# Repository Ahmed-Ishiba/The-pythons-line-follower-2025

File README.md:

# Robocup-The Pythons

This is a documentation of our journey in the Robocup competition in line-follower category, the team members are Ahmed Ibrahim Elsayed (me), Moaz Ahmed, Eyad Ahmed, Nour Eldin Raoof each are responsible for the programming , electrical and Mechanical part of the robot respectively and our coach Omar Ahmed Khaled.

This documentation will list the components used , the thought process that went into making this robot and the algorithm of our line-following and evacuation zone

## Compontents used:
| Name | Price | Weight | Link|
|------|-------|--------|-----|
|Pololu wheels|9.95 USD|23gm|https://www.pololu.com/product/3691|
|Omni wheels|35 USD| 49gm|https://www.robotshop.com/products/70mm-omni-wheel-4mm-bore |
|133rpm Motors| 360 EGP|88gm|https://makerselectronics.com/product/dc-motor-with-gear-box-jga25-370-12v-133rpm-20kg-cm |
|Raspberry pi5 8gb ram| 80USD|76gm|https://www.adafruit.com/product/5813|
|Raspberry pi camera module3|35 USD|5gm|https://www.adafruit.com/product/5658|
|Adafruit DRV8871 motor driver|7.5 USD|5gm|https://www.adafruit.com/product/3190|
|Adafruit Time of Flight sensor|14.95 USD|2gm|https://www.adafruit.com/product/3317|
|10 DOF IMU|920 EGP|2gm|https://store.fut-electronics.com/products/10-dof-imu-mpu9250-bmp280?_pos=3&_sid=8a9a77714&_ss=r |
|InfraRed obstacle sensor|75 EGP|3gm|https://store.fut-electronics.com/products/infrared-obstacle-avoidance-sensor-ky-032?_pos=1&_sid=9cff58162&_ss=r|
|Microservo MG90S|140 EGP|17gm|https://makerselectronics.com/product/micro-servo-mg90s-full-metal-gear-180-degree|
|Hiwonder full metal gear|18.99 USD |101gm|https://www.hiwonder.com/products/hps-2018?_pos=16&_sid=3165c6d7c&_ss=r|
|XL 4015 step down dc convertor|115 EGP| 21 gm|https://makerselectronics.com/product/xl4015-step-down-dc-module-with-cv-cc-control|
|LM-2596S DC-DC convertor| 55 EGP |13gm|https://makerselectronics.com/product/lm2596s-dc-dc-converter-3a-step-down-module|
|XL-4016 Step down convertos| 260 EGP|75 gm | https://ampere-electronics.com/product/xl4016-dc-dc-step-down-converter-module-12a-300w/|
|Cytron dual channel motor driver| 1750 EGP | 33gm| https://store.fut-electronics.com/products/dual-channel-dc-motor-driver-10a-each|

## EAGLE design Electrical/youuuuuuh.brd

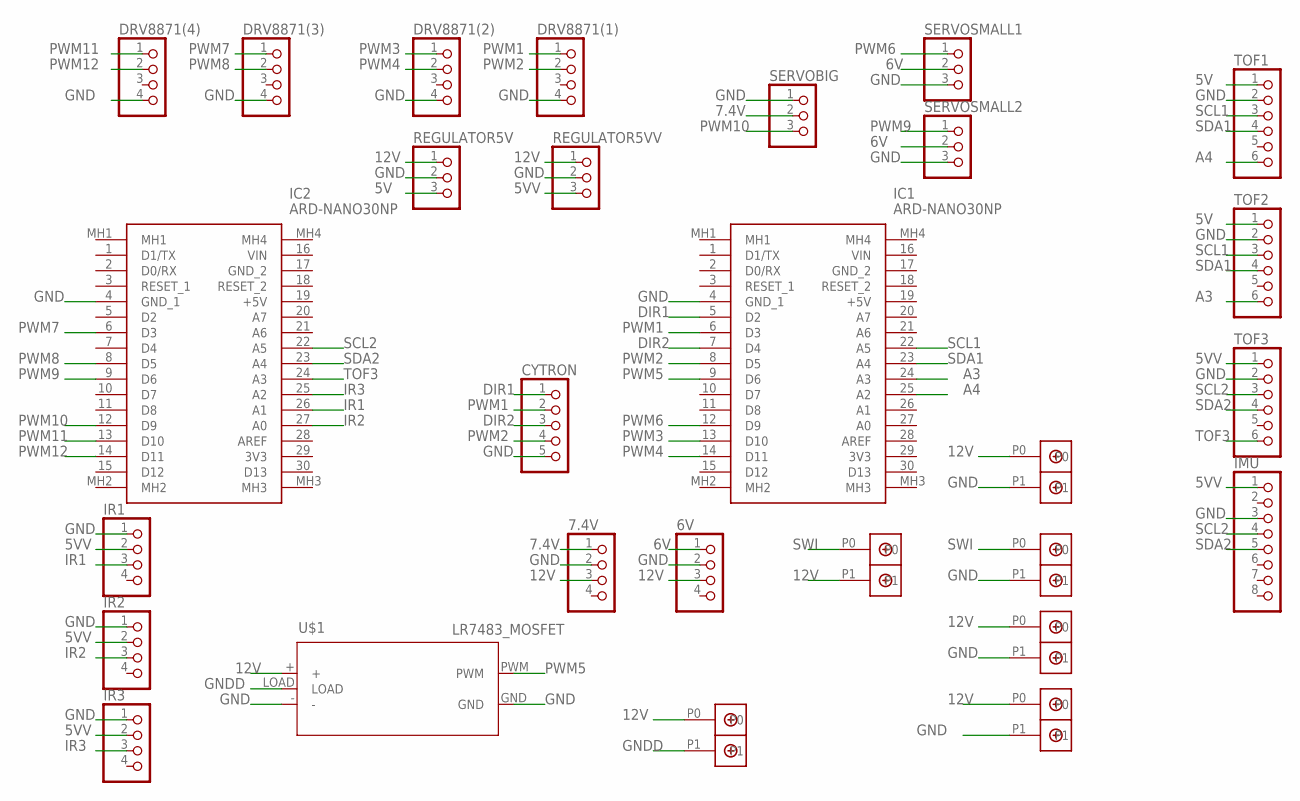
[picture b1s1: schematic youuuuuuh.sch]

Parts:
6V, 7.4V: PINHD-1X4; 1X04
BATERY: DBCONN-1X2
BUCKSERVO: DBCONN-1X2
CYTRON: PINHD-1X5; 1X05
CYTRONPOWER: DBCONN-1X2
DRV8871(1), DRV8871(2), DRV8871(3), DRV8871(4): PINHD-1X4; 1X04
IC1, IC2: ARD-NANO30NP; ARDNANO30NP
IMU: PINHD-1X8; 1X08
IR1, IR2, IR3: PINHD-1X4; 1X04
LEDS1, LEDS2, LEDS3: DBCONN-1X2
REGULATOR5V, REGULATOR5VV: PINHD-1X3; 1X03
SERVOBIG: PINHD-1X3; 1X03
SERVOSMALL1, SERVOSMALL2: PINHD-1X3; 1X03
TOF1, TOF2, TOF3: PINHD-1X6; 1X06
U$1: LR7483_MOSFET

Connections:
5V: REGULATOR5V.3, TOF1.1, TOF2.1
5VV: IMU.1, IR1.2, IR2.2, IR3.2, REGULATOR5VV.3, TOF3.1
6V: 6V.1, SERVOSMALL1.2, SERVOSMALL2.2
7.4V: 7.4V.1, SERVOBIG.2
12V: 6V.3, 7.4V.3, BUCKSERVO.P0, CYTRONPOWER.P0, LEDS1.P1, LEDS2.P0, LEDS3.P0, REGULATOR5V.1, REGULATOR5VV.1, U$1.+
A3: IC1.24 (A3), TOF2.6
A4: IC1.25 (A2), TOF1.6
DIR1: CYTRON.1, IC1.5 (D2)
DIR2: CYTRON.3, IC1.7 (D4)
GND: 6V.2, 7.4V.2, BATERY.P1, BUCKSERVO.P1, CYTRON.5, CYTRONPOWER.P1, DRV8871(1).4, DRV8871(2).4, DRV8871(3).4, DRV8871(4).4, IC1.4 (GND_1), IC2.4 (GND_1), IMU.3, IR1.1, IR2.1, IR3.1, LEDS2.P1, REGULATOR5V.2, REGULATOR5VV.2, SERVOBIG.1, SERVOSMALL1.3, SERVOSMALL2.3, TOF1.2, TOF2.2, TOF3.2, U$1.-, U$1.GND
GNDD: LEDS3.P1, U$1.LOAD
IR1: IC2.26 (A1), IR1.3
IR2: IC2.27 (A0), IR2.3
IR3: IC2.25 (A2), IR3.3
PWM1: CYTRON.2, DRV8871(1).1, IC1.6 (D3)
PWM2: CYTRON.4, DRV8871(1).2, IC1.8 (D5)
PWM3: DRV8871(2).1, IC1.13 (D10)
PWM4: DRV8871(2).2, IC1.14 (D11)
PWM5: IC1.9 (D6), U$1.PWM
PWM6: IC1.12 (D9), SERVOSMALL1.1
PWM7: DRV8871(3).1, IC2.6 (D3)
PWM8: DRV8871(3).2, IC2.8 (D5)
PWM9: IC2.9 (D6), SERVOSMALL2.1
PWM10: IC2.12 (D9), SERVOBIG.3
PWM11: DRV8871(4).1, IC2.13 (D10)
PWM12: DRV8871(4).2, IC2.14 (D11)
SCL1: IC1.22 (A5), TOF1.3, TOF2.3
SCL2: IC2.22 (A5), IMU.4, TOF3.3
SDA1: IC1.23 (A4), TOF1.4, TOF2.4
SDA2: IC2.23 (A4), IMU.5, TOF3.4
SWI: BATERY.P0, LEDS1.P0
TOF3: IC2.24 (A3), TOF3.6

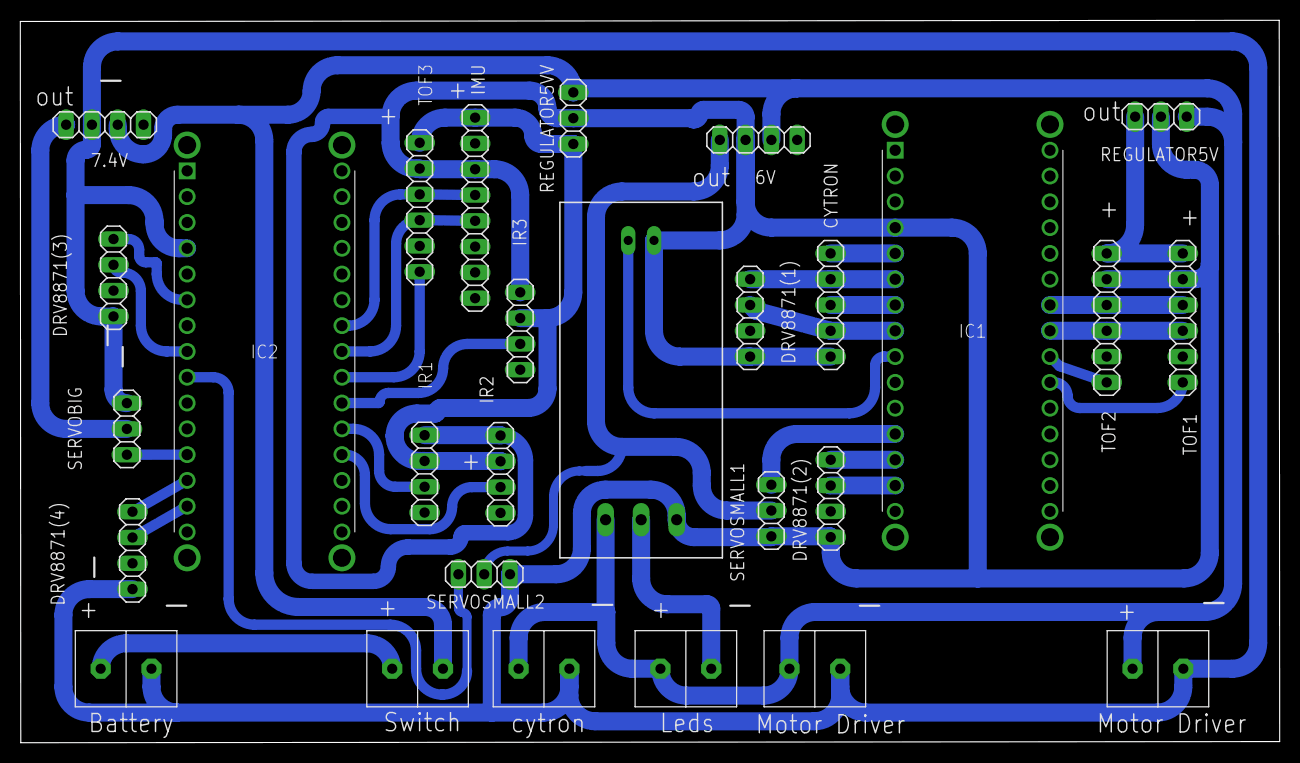
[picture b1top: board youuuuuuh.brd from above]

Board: 2 copper layers, 124.0 x 71.1 mm, 28 parts (0 on the bottom side), 32 nets.

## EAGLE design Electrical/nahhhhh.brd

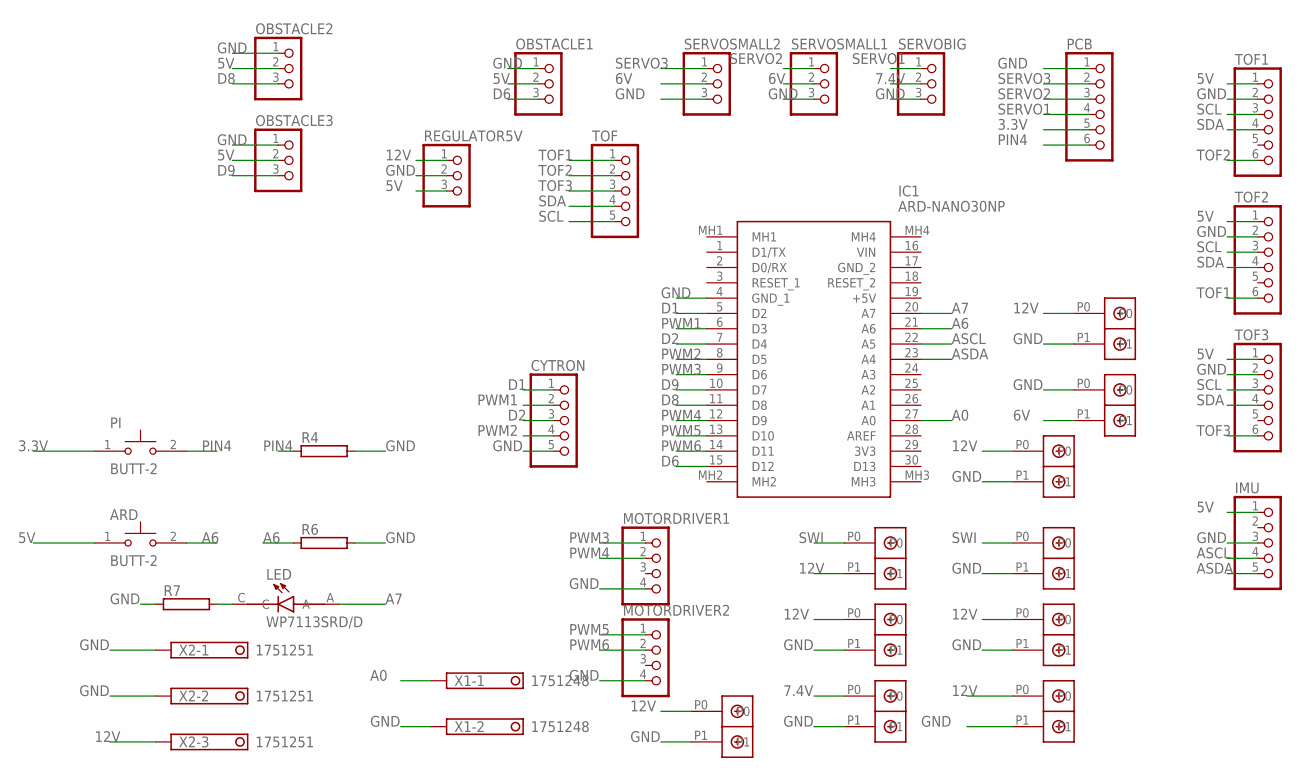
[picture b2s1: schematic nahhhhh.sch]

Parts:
ARD: BUTT-2; SW_BUTT-2
BATERY: DBCONN-1X2
BUCKSERVO: DBCONN-1X2
CYTRON: PINHD-1X5; 1X05
CYTRONPOWER: DBCONN-1X2
IC1: ARD-NANO30NP; ARDNANO30NP
IMU: PINHD-1X5; 1X05
LED: WP7113SRD/D; LED_WP7113SRD/D
LEDS, LEDS1, LEDS2, LEDS3, LEDS4, LEDS5: DBCONN-1X2
MOTORDRIVER1, MOTORDRIVER2: PINHD-1X4; 1X04
OBSTACLE1, OBSTACLE2, OBSTACLE3: PINHD-1X3; 1X03
PCB: PINHD-1X6; 1X06
PI: BUTT-2; SW_BUTT-2
R4, R6, R7: RHPS58; HPS58
REGULATOR5V: PINHD-1X3; 1X03
SERVOBIG: PINHD-1X3; 1X03
SERVOSMALL1, SERVOSMALL2: PINHD-1X3; 1X03
TOF: PINHD-1X5; 1X05
TOF1, TOF2, TOF3: PINHD-1X6; 1X06
U$1: DBCONN-1X2
X1: 1751248
X2: 1751251

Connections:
3.3V: PCB.5, PI.1
5V: ARD.1, IMU.1, OBSTACLE1.2, OBSTACLE2.2, OBSTACLE3.2, REGULATOR5V.3, TOF1.1, TOF2.1, TOF3.1
6V: LEDS5.P1, SERVOSMALL1.2, SERVOSMALL2.2
7.4V: SERVOBIG.2, U$1.P0
12V: BUCKSERVO.P0, CYTRONPOWER.P0, LEDS.P0, LEDS1.P1, LEDS2.P0, LEDS3.P0, LEDS4.P0, REGULATOR5V.1, X2.3
A0: IC1.27 (A0), X1.1
A6: ARD.2, IC1.21 (A6), R6.1
A7: IC1.20 (A7), LED.A
ASCL: IC1.22 (A5), IMU.4
ASDA: IC1.23 (A4), IMU.5
D1: CYTRON.1, IC1.5 (D2)
D2: CYTRON.3, IC1.7 (D4)
D6: IC1.15 (D12), OBSTACLE1.3
D8: IC1.11 (D8), OBSTACLE2.3
D9: IC1.10 (D7), OBSTACLE3.3
GND: BATERY.P1, BUCKSERVO.P1, CYTRON.5, CYTRONPOWER.P1, IC1.4 (GND_1), IMU.3, LEDS.P1, LEDS2.P1, LEDS3.P1, LEDS4.P1, LEDS5.P0, MOTORDRIVER1.4, MOTORDRIVER2.4, OBSTACLE1.1, OBSTACLE2.1, OBSTACLE3.1, PCB.1, R4.2, R6.2, R7.1, REGULATOR5V.2, SERVOBIG.3, SERVOSMALL1.3, SERVOSMALL2.3, TOF1.2, TOF2.2, TOF3.2, U$1.P1, X1.2, X2.1, X2.2
unnamed: LED.C, R7.2
PIN4: PCB.6, PI.2, R4.1
PWM1: CYTRON.2, IC1.6 (D3)
PWM2: CYTRON.4, IC1.8 (D5)
PWM3: IC1.9 (D6), MOTORDRIVER1.1
PWM4: IC1.12 (D9), MOTORDRIVER1.2
PWM5: IC1.13 (D10), MOTORDRIVER2.1
PWM6: IC1.14 (D11), MOTORDRIVER2.2
SCL: TOF.5, TOF1.3, TOF2.3, TOF3.3
SDA: TOF.4, TOF1.4, TOF2.4, TOF3.4
SERVO1: PCB.4, SERVOBIG.1
SERVO2: PCB.3, SERVOSMALL1.1
SERVO3: PCB.2, SERVOSMALL2.1
SWI: BATERY.P0, LEDS1.P0
TOF1: TOF.1, TOF2.6
TOF2: TOF.2, TOF1.6
TOF3: TOF.3, TOF3.6

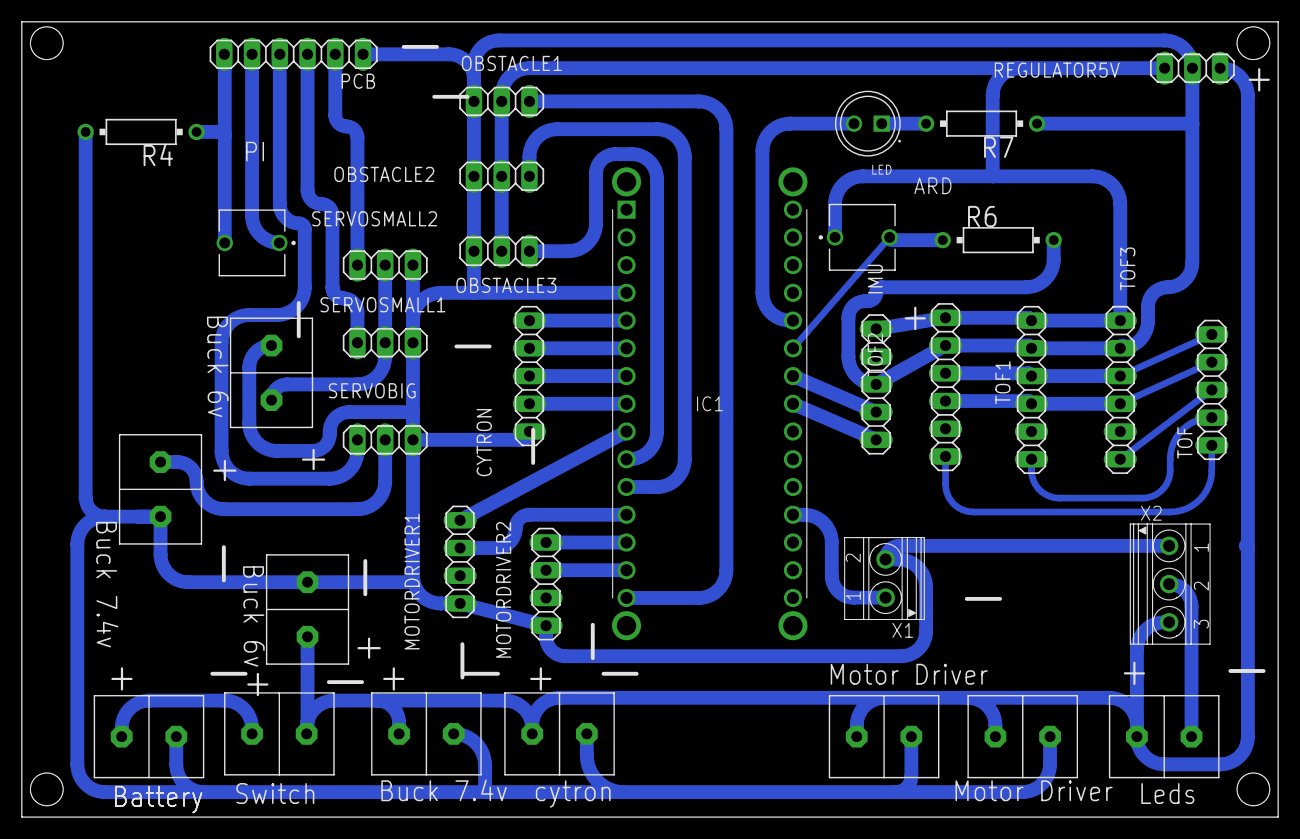
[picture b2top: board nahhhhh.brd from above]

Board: 2 copper layers, 115.0 x 72.8 mm, 35 parts (0 on the bottom side), 33 nets.

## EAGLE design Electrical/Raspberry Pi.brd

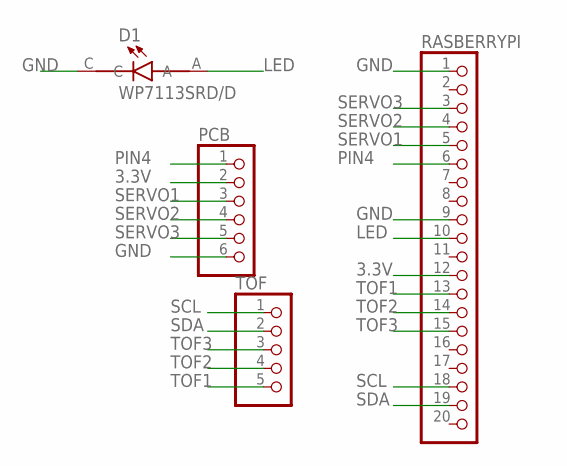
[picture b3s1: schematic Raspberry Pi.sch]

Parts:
D1: WP7113SRD/D; LED_WP7113SRD/D
PCB: PINHD-1X6; 1X06
RASBERRYPI: PINHD-1X20; 1X20
TOF: PINHD-1X5; 1X05

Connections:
3.3V: PCB.2, RASBERRYPI.12
GND: D1.C, PCB.6, RASBERRYPI.1, RASBERRYPI.9
LED: D1.A, RASBERRYPI.10
PIN4: PCB.1, RASBERRYPI.6
SCL: RASBERRYPI.18, TOF.1
SDA: RASBERRYPI.19, TOF.2
SERVO1: PCB.3, RASBERRYPI.5
SERVO2: PCB.4, RASBERRYPI.4
SERVO3: PCB.5, RASBERRYPI.3
TOF1: RASBERRYPI.13, TOF.5
TOF2: RASBERRYPI.14, TOF.4
TOF3: RASBERRYPI.15, TOF.3

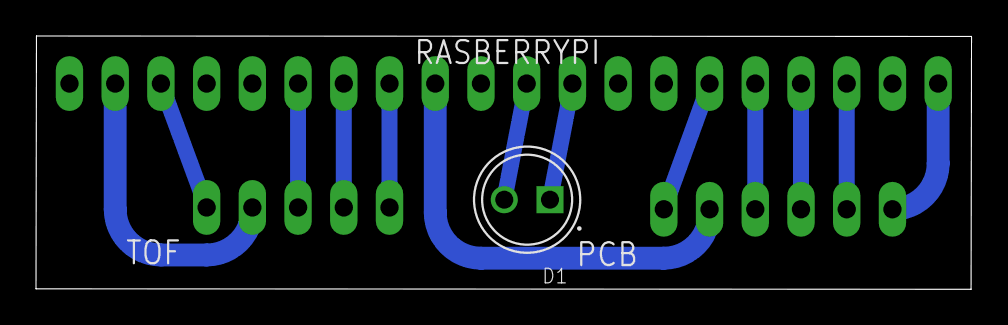
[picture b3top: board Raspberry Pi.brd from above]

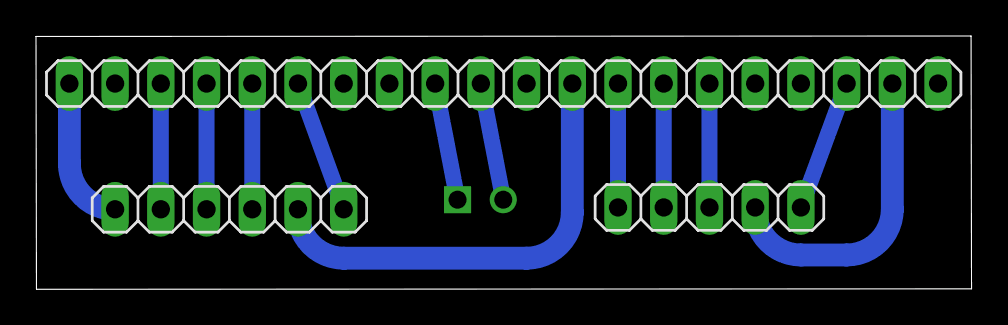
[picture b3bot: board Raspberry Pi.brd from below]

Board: 2 copper layers, 52.0 x 14.1 mm, 4 parts (3 on the bottom side), 12 nets.

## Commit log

2024-09-13 Create placeholder
2024-09-13 The Solidpart For The Lower And Upper Floor Of The Robot
2024-09-13 Create Previews
2025-04-21 Upload code
